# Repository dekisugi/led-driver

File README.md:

[LED照明を作ってみた](https://elchika.com/article/85ea9703-cf6b-4a59-984c-5e45b06b6c70/)([ミラー](https://geeko.dev/one/2021/02/28/led-driver/))のソース、KiCadファイル置き場。

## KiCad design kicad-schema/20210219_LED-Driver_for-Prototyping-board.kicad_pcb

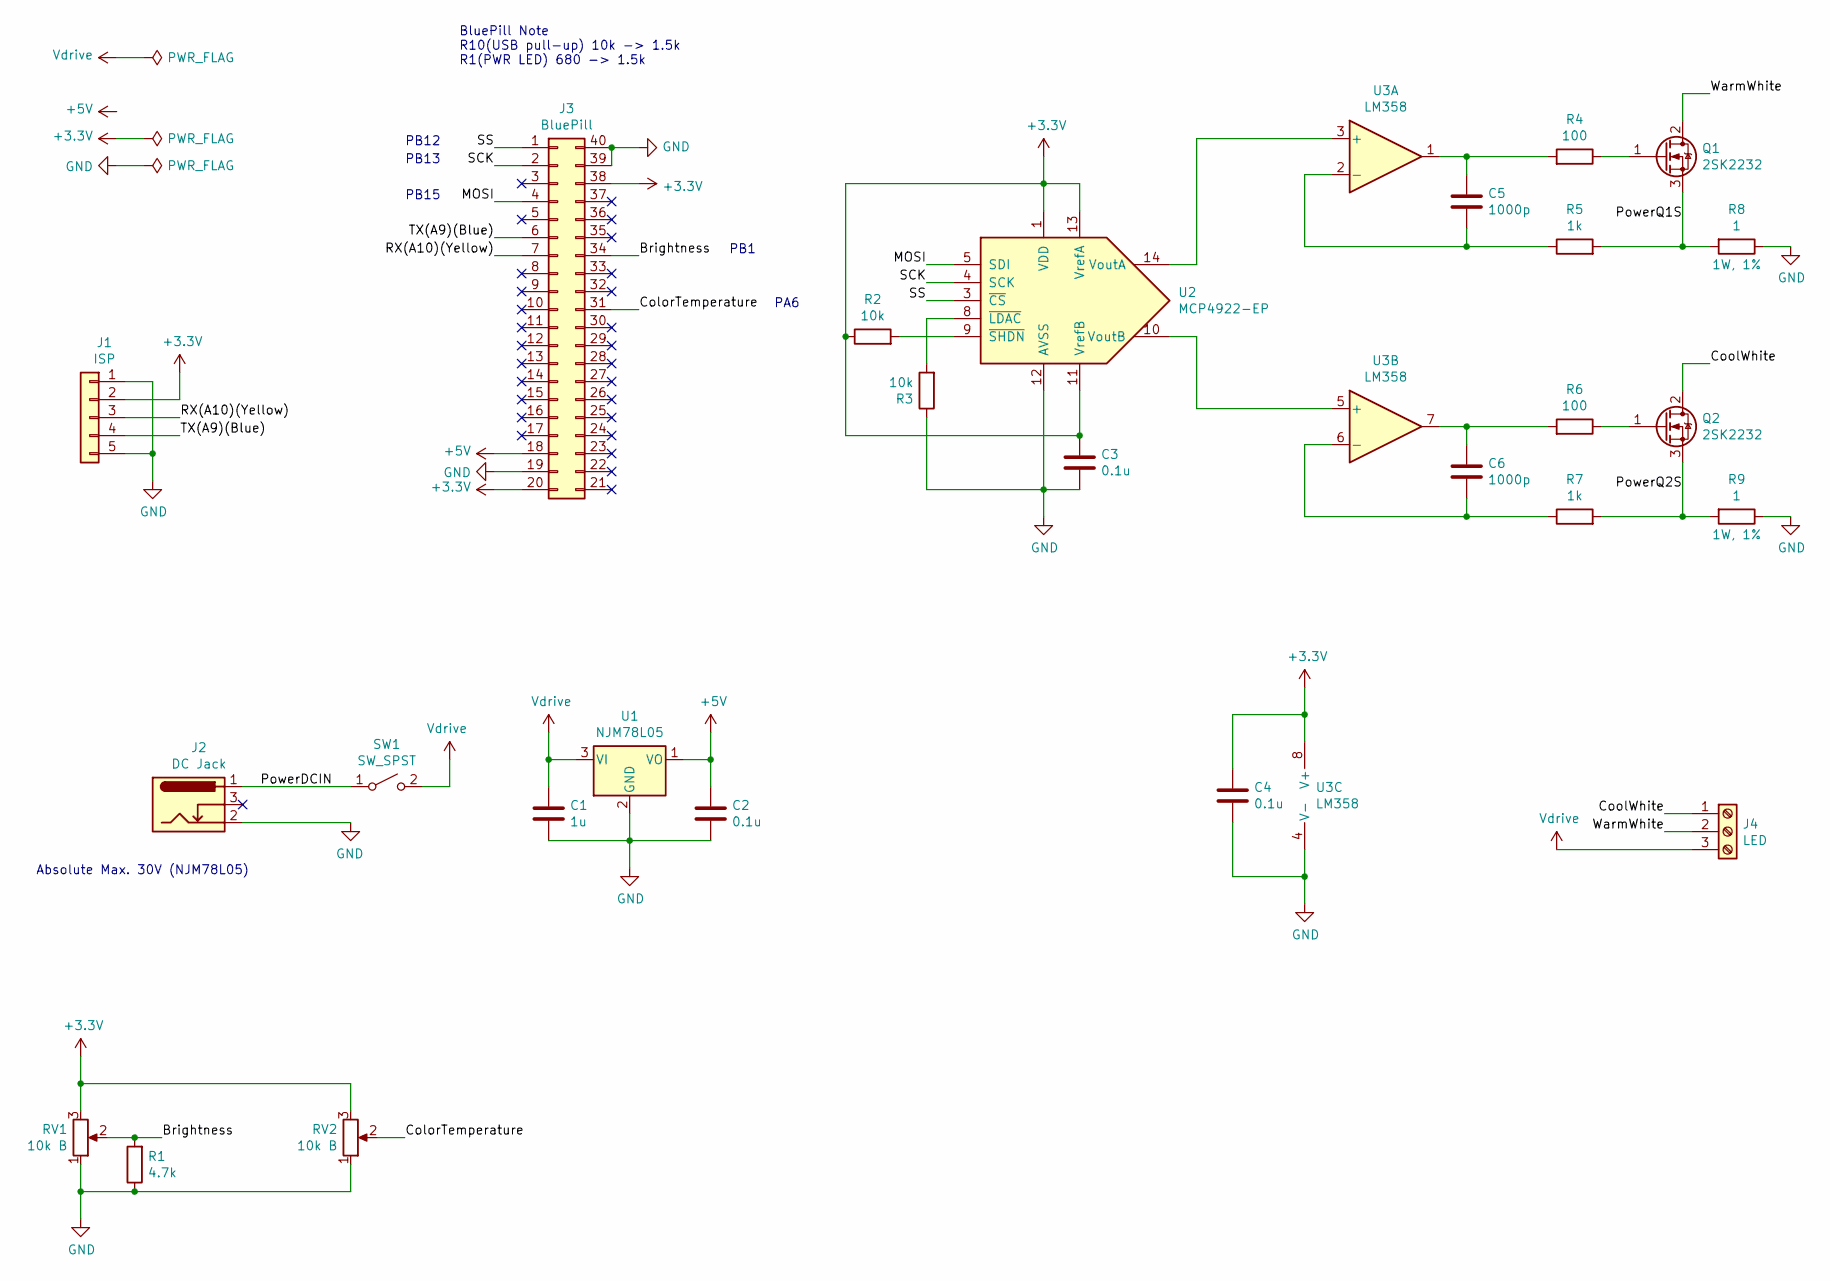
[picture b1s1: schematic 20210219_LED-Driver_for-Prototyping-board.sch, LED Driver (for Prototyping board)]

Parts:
C1: 1u; C_Disc_D3.8mm_W2.6mm_P2.50mm; Part Number RD15F105Z1HL2L
C2, C3, C4: 0.1u; C_0805_2012Metric; Part Number GRM40F104Z50
C5, C6: 1000p; C_Disc_D3.8mm_W2.6mm_P2.50mm
J1: ISP; PinHeader_1x05_P2.54mm_Vertical
J2: DC Jack; BarrelJack_Horizontal; Part Number 18742
J3: BluePill; DIP-40_W15.24mm_Socket
J4: LED; TerminalBlock_Phoenix_MKDS-1,5-3-5.08_1x03_P5.08mm_Horizont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; Part Number APF-103
Q1, Q2: 2SK2232; TO-220-3_Vertical; Part Number 2SK2232
R1: 4.7k; R_Axial_DIN0207_L6.3mm_D2.5mm_P2.54mm_Vertical
R2, R3: 10k; R_Axial_DIN0207_L6.3mm_D2.5mm_P10.16mm_Horizontal
R4, R6: 100; R_Axial_DIN0207_L6.3mm_D2.5mm_P2.54mm_Vertical
R5, R7: 1k; R_Axial_DIN0207_L6.3mm_D2.5mm_P2.54mm_Vertical
R8, R9: 1; R_Axial_DIN0414_L11.9mm_D4.5mm_P15.24mm_Horizontal; Part Number Metal film Resistor
RV1, RV2: 10k B; PinHeader_1x03_P2.54mm_Vertical
SW1: SW_SPST; PinHeader_1x02_P2.54mm_Vertical
U1: NJM78L05; TO-92_Inline_Wide; Part Number NJM78L05L2A
U2: MCP4922-EP; DIP-14_W7.62mm_Socket; Part Number MCP4922-E/P
U3: LM358; DIP-8_W7.62mm_Socket; Part Number LM358N

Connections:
+3V3: C3.1, C4.1, J1.2, J3.20, J3.38, R2.1, RV1.3, RV2.3, U2.1 (VDD), U2.11 (VrefB), U2.13 (VrefA), U3.8 (V+)
+5V: C2.1, J3.18, U1.1 (VO)
/Brightness: J3.34, R1.2, RV1.2
/ColorTemperature: J3.31, RV2.2
/CoolWhite: J4.1, Q2.2 (D)
/MOSI: J3.4, U2.5 (SDI)
/PowerDCIN: J2.1, SW1.1 (A)
/PowerQ1S: Q1.3 (S), R5.2, R8.2
/PowerQ2S: Q2.3 (S), R7.2, R9.2
/RX(A10)(Yellow): J1.3, J3.7
/SCK: J3.2, U2.4 (SCK)
/SS: J3.1, U2.3 (~CS~)
/TX(A9)(Blue): J1.4, J3.6
/WarmWhite: J4.2, Q1.2 (D)
GND: C1.2, C2.2, C3.2, C4.2, J1.1, J1.5, J2.2, J3.19, J3.39, J3.40, R1.1, R3.1, R8.1, R9.1, RV1.1, RV2.1, U1.2 (GND), U2.12 (AVSS), U3.4 (V-)
unnamed: C5.1, R4.2, U3.1
unnamed: C5.2, R5.1, U3.2 (-)
unnamed: C6.1, R6.2, U3.7
unnamed: C6.2, R7.1, U3.6 (-)
unnamed: Q1.1 (G), R4.1
unnamed: Q2.1 (G), R6.1
unnamed: R2.2, U2.9 (~SHDN~)
unnamed: R3.2, U2.8 (~LDAC~)
unnamed: U2.10 (VoutB), U3.5 (+)
unnamed: U2.14 (VoutA), U3.3 (+)
Vdrive: C1.1, J4.3, SW1.2 (B), U1.3 (VI)

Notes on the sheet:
BluePill Note R10(USB pull-up) 10k -> 1.5k R1(PWR LED) 680 -> 1.5k
Absolute Max. 30V (NJM78L05)
PB12
PB13
PB15
PA6
PB1

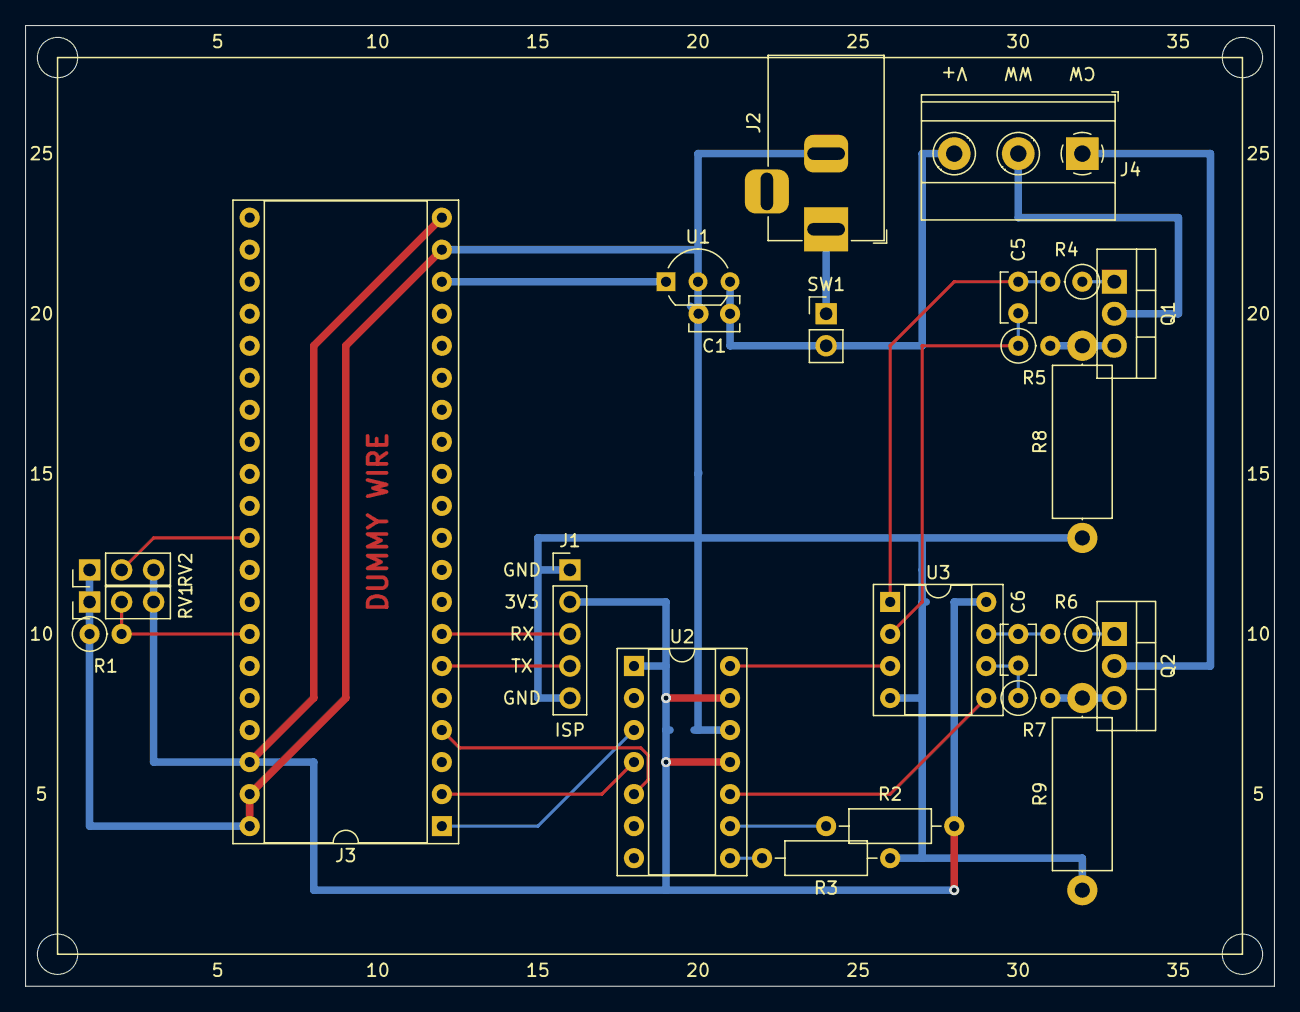
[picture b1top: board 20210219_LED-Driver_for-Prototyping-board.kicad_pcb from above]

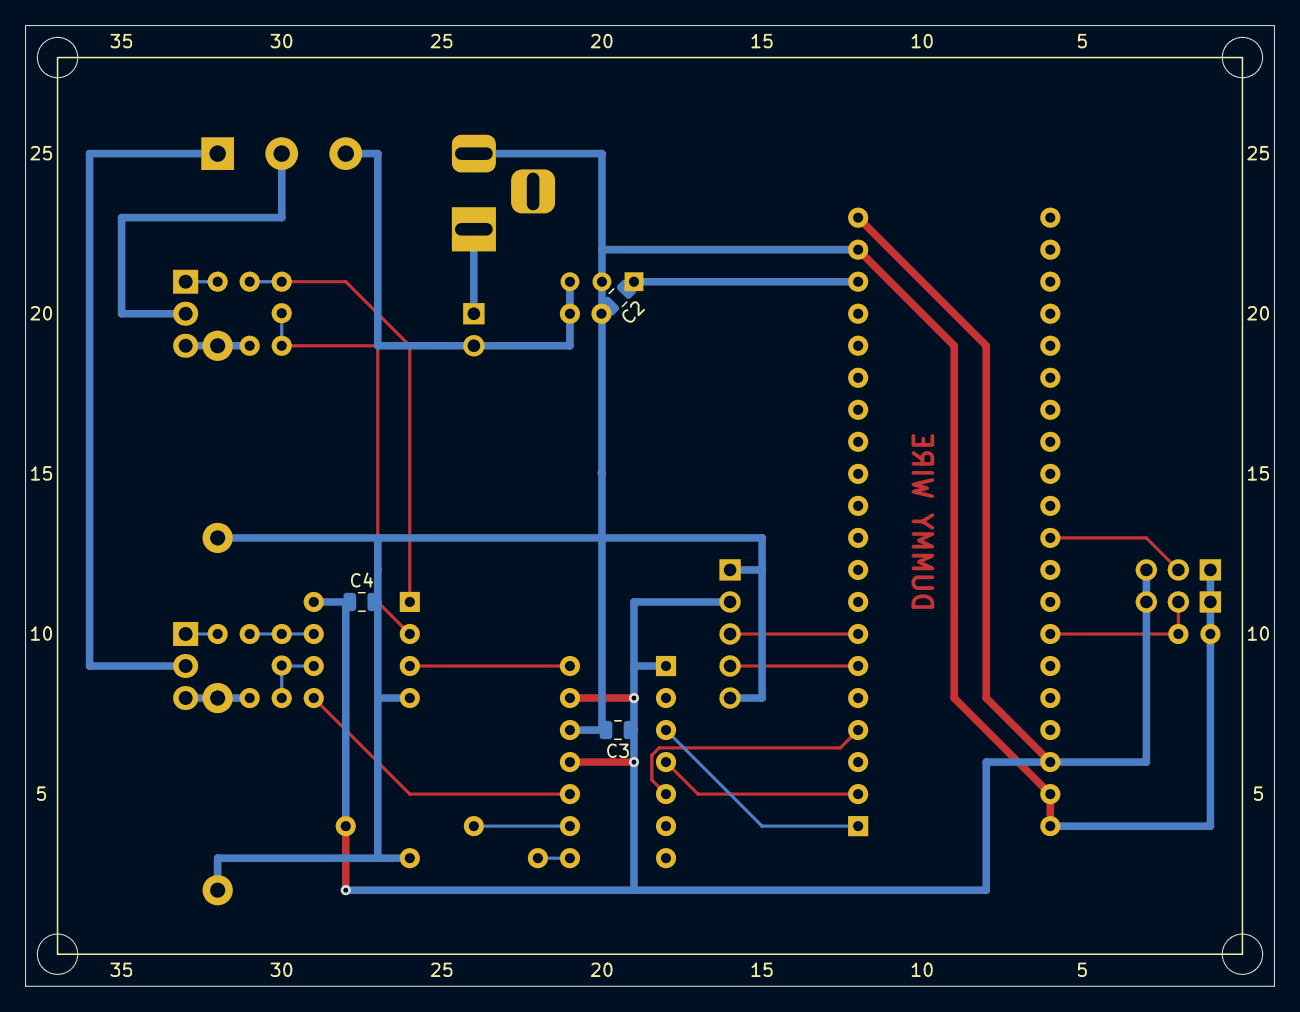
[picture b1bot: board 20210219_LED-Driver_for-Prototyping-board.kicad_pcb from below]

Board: 2 copper layers, 99.1 x 76.2 mm, 27 parts (3 on the bottom side), 26 nets.

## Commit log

2021-02-28 中身を放り込む。
2021-02-28 README.mdを編集。
